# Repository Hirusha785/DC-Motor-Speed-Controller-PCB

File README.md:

# DC Motor Speed Controller PCB

A compact DC motor speed controller PCB designed in KiCad using an **NE555 timer IC** configured as a PWM generator and a **TIP122 Darlington transistor** as the motor driver stage.

This project is suitable for controlling the speed of small DC motors using a potentiometer-based PWM control method.

---

## 📌 Project Overview

This PCB is designed to control the speed of a DC motor by varying the duty cycle of a PWM signal generated by the NE555 timer. The output PWM signal drives a TIP122 transistor, allowing the connected DC motor to run at adjustable speeds.

The board includes screw terminal connectors for power input and motor output, an onboard power indicator LED, and mounting holes for easy installation.

---

## ⚙️ Features

- NE555-based PWM speed control
- Adjustable speed using potentiometer
- TIP122 transistor motor driver
- Flyback diode protection for motor load
- Power indicator LED
- Screw terminal input and output connectors
- Compact single-board layout
- Designed using KiCad
- Includes schematic, PCB layout, and 3D PCB renders

---

## 🧩 Main Components

| Reference | Component | Description |
|---|---|---|
| U1 | NE555P | Timer IC used for PWM generation |
| Q1 | TIP122 | NPN Darlington transistor used as motor driver |
| RV1 | 100K Potentiometer | Speed adjustment control |
| D1, D2, D3 | 1N4007 | Diodes for timing and motor protection |
| D4 | LED | Power indicator |
| C1, C2 | 100nF | Timing / filtering capacitors |
| C3 | 100uF | Power supply smoothing capacitor |
| R1, R2 | 1K | Current limiting / base drive resistors |
| R3 | 2.2K | LED current limiting resistor |
| J1 | Screw Terminal | DC power input |
| J2 | Screw Terminal | DC motor output |

---

## 🔌 Circuit Description

The NE555 timer IC is configured in astable PWM mode. The potentiometer changes the charge and discharge path of the timing capacitor, allowing the duty cycle of the output signal to be adjusted.

The PWM output from pin 3 of the NE555 drives the TIP122 transistor through a base resistor. The TIP122 switches the motor current on and off rapidly according to the PWM duty cycle.

A flyback diode is connected across the motor output to protect the transistor from reverse voltage spikes generated by the motor coil.

---

## 🖥️ PCB Design

The PCB was designed in KiCad and includes:

- Schematic design
- PCB routing
- 3D component placement
- Through-hole components for easy soldering
- Large terminal blocks for motor and power connections
- Mounting holes at all four corners

---

## 📷 Project Images

### Schematic

### PCB Layout

### 3D View

---

## 👨‍💻 Author

Designed by Fernando S.M.H.G.

PCB designed using KiCad.

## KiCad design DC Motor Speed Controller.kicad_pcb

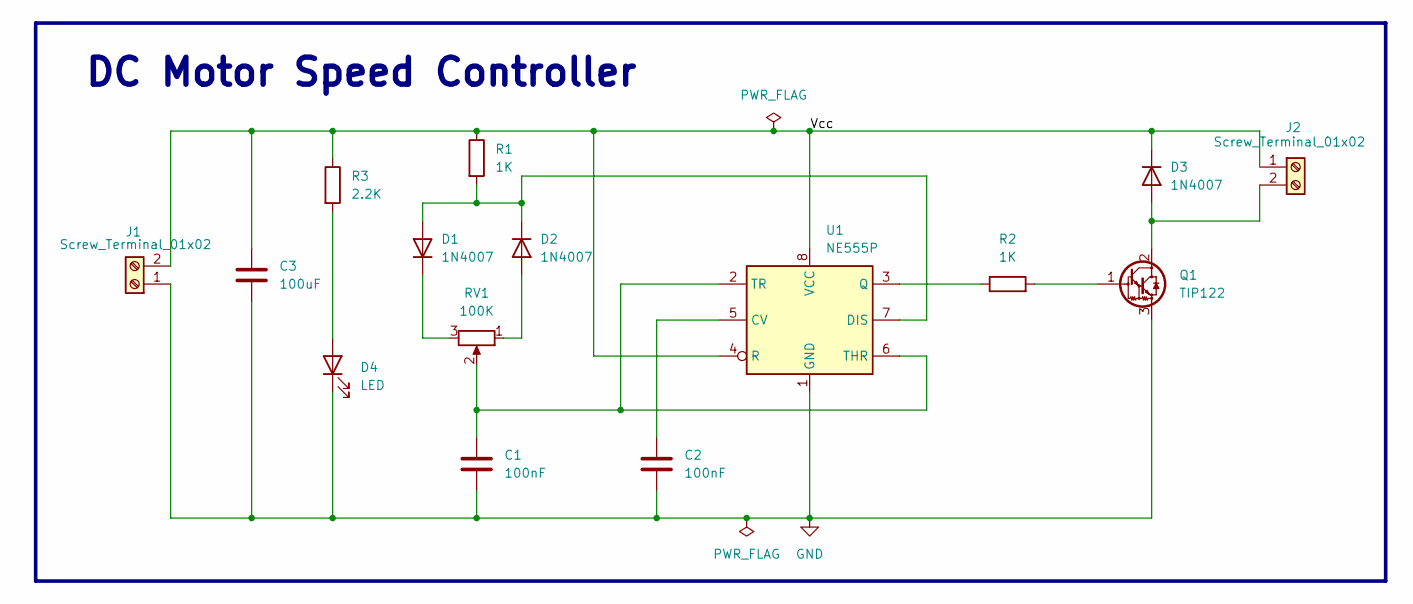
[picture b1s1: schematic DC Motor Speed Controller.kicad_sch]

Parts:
C1, C2: 100nF; C_Disc_D7.0mm_W2.5mm_P5.00mm
C3: 100uF; CP_Radial_D10.0mm_P5.00mm
D1, D2, D3: 1N4007; D_DO-41_SOD81_P10.16mm_Horizontal
D4: LED; LED_D4.0mm
J1, J2: Screw_Terminal_01x02; TerminalBlock_bornier-2_P5.08mm
Q1: TIP122; TO-220-3_Vertical
R1: 1K; R_Axial_DIN0207_L6.3mm_D2.5mm_P10.16mm_Horizontal
R2: 1K; R_Axial_DIN0204_L3.6mm_D1.6mm_P5.08mm_Horizontal
R3: 2.2K; R_Axial_DIN0207_L6.3mm_D2.5mm_P10.16mm_Horizontal
RV1: 100K; Potentiometer_Piher_PC-16_Single_Horizontal
U1: NE555P; DIP-8_W7.62mm

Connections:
/Vcc: C3.2, D3.1 (K), J1.2, J2.1, R1.1, R3.1, U1.4 (R), U1.8 (VCC)
GND: C1.2, C2.2, C3.1, D4.1 (K), J1.1, Q1.3 (E), U1.1 (GND)
unnamed: D1.2 (A), D2.1 (K), R1.2, U1.7 (DIS)
unnamed: D1.1 (K), RV1.3
unnamed: D2.2 (A), RV1.1
unnamed: D3.2 (A), J2.2, Q1.2 (C)
unnamed: D4.2 (A), R3.2
unnamed: Q1.1 (B), R2.2
unnamed: C2.1, U1.5 (CV)
unnamed: R2.1, U1.3 (Q)
unnamed: C1.1, RV1.2, U1.2 (TR), U1.6 (THR)

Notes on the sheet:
DC Motor Speed Controller

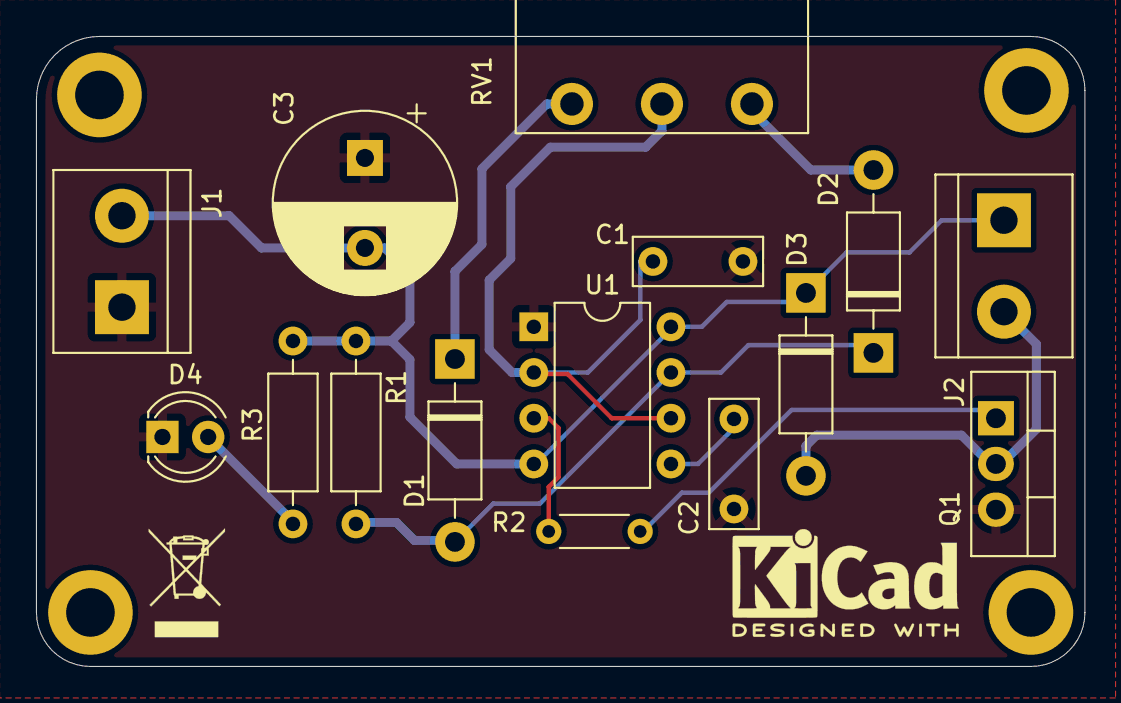
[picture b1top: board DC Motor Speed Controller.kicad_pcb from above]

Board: 2 copper layers, 58.2 x 35.0 mm, 15 parts (0 on the bottom side), 11 nets.
